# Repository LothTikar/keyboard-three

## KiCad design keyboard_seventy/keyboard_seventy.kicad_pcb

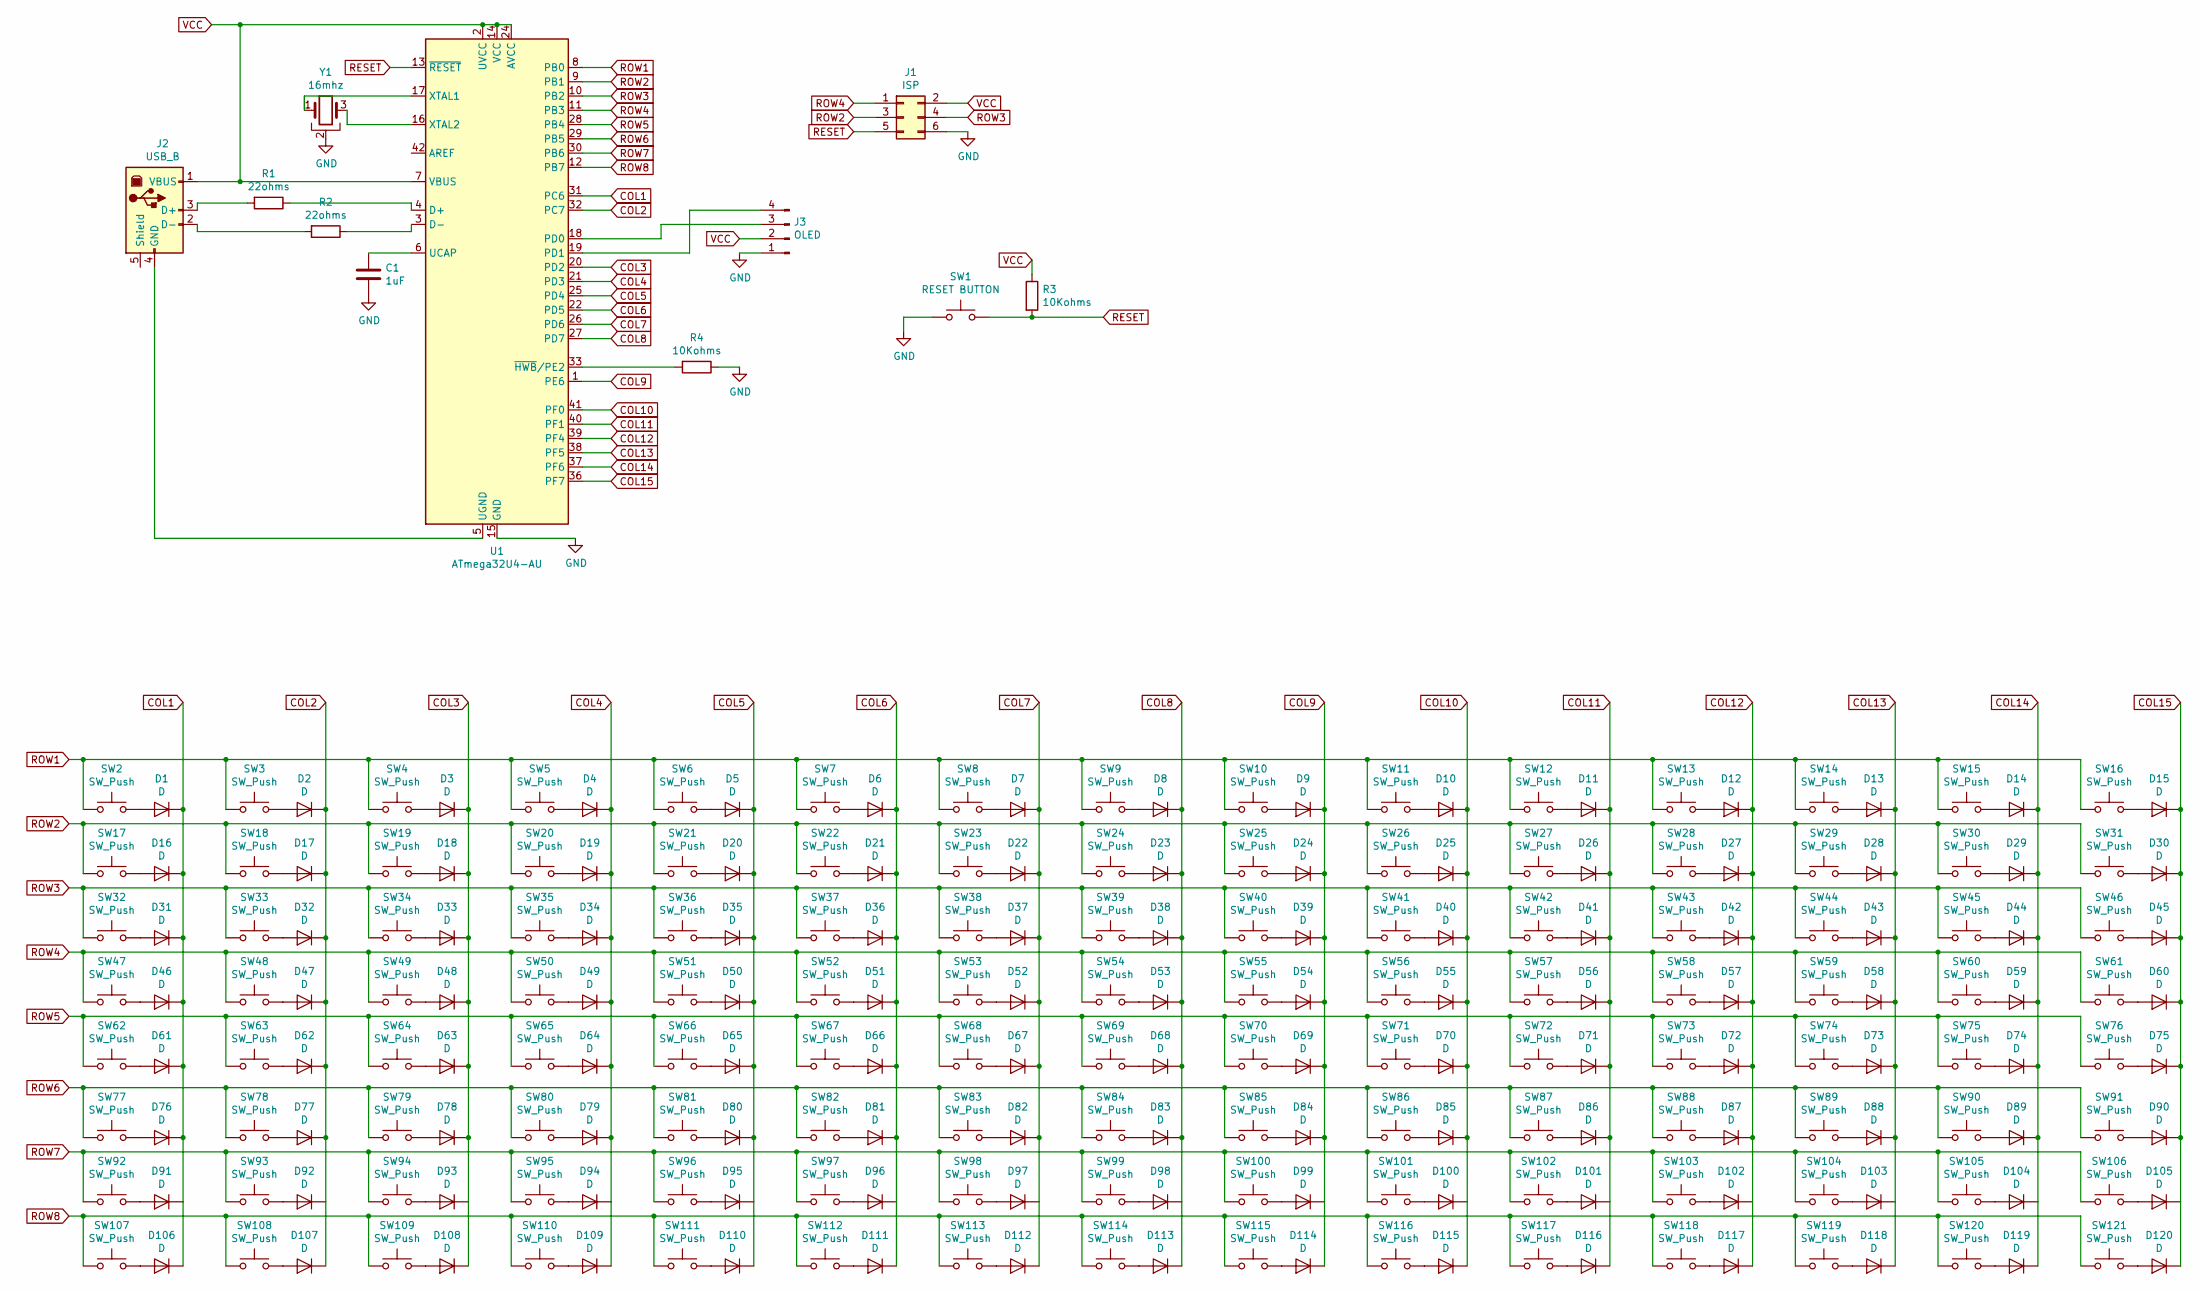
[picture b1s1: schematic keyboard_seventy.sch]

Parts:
C1: 1uF; C_Disc_D3.0mm_W1.6mm_P2.50mm
D1, D2, D3, D4, D5, D6, D7, D8, D9, D10, D11, D12, D13, D14, D15, D16, D17, D18, D19, D20, D21, D22, D23, D24, D25, D26, D27, D28, D29, D30, D31, D32, D33, D34, D35, D36, D37, D38, D39, D40, D41, D42, D43, D44, D45, D46, D47, D48, D49, D50, D51, D52, D53, D54, D55, D56, D57, D58, D59, D60, D61, D62, D63, D64, D65, D66, D67, D68, D69, D70, D71, D72, D73, D74, D75, D76, D77, D78, D79, D80, D81, D82, D83, D84, D85, D86, D87, D88, D89, D90, D91, D92, D93, D94, D95, D96, D97, D98, D99, D100, D101, D102, D103, D104, D105, D106, D107, D108, D109, D110, D111, D112, D113, D114, D115, D116, D117, D118, D119, D120: D; D_A-405_P7.62mm_Horizontal
J1: ISP; PinHeader_2x03_P2.54mm_Vertical
J2: USB_B; USB_B_OST_USB-B1HSxx_Horizontal
J3: OLED; PinHeader_1x04_P2.54mm_Vertical
R1, R2: 22ohms; R_Axial_DIN0207_L6.3mm_D2.5mm_P10.16mm_Horizontal
R3, R4: 10Kohms; R_Axial_DIN0207_L6.3mm_D2.5mm_P10.16mm_Horizontal
SW1: RESET BUTTON; SW_PUSH-12mm
SW2, SW3, SW4, SW5, SW6, SW7, SW8, SW9, SW10, SW11, SW12, SW13, SW14, SW15, SW16, SW17, SW18, SW19, SW20, SW21, SW22, SW23, SW24, SW25, SW26, SW27, SW28, SW29, SW30, SW31, SW32, SW33, SW34, SW35, SW36, SW37, SW38, SW39, SW40, SW41, SW42, SW43, SW44, SW45, SW46, SW47, SW48, SW49, SW50, SW51, SW52, SW53, SW54, SW55, SW56, SW57, SW58, SW59, SW60, SW61, SW62, SW63, SW64, SW65, SW66, SW67, SW68, SW69, SW70, SW71, SW72, SW73, SW74, SW75, SW76, SW77, SW78, SW79, SW80, SW81, SW82, SW83, SW84, SW85, SW86, SW87, SW88, SW89, SW90, SW91, SW92, SW93, SW94, SW95, SW96, SW97, SW98, SW99, SW100, SW101, SW102, SW103, SW104, SW105, SW106, SW107, SW108, SW109, SW110, SW111, SW112, SW113, SW114, SW115, SW116, SW117, SW118, SW119, SW120, SW121: SW_Push; PG1350_socket
U1: ATmega32U4-AU; TQFP-44_10x10mm_P0.8mm
Y1: 16mhz; Resonator-3Pin_W10.0mm_H5.0mm

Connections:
COL1: D1.1 (K), D16.1 (K), D31.1 (K), D46.1 (K), D61.1 (K), D76.1 (K), D91.1 (K), D106.1 (K), U1.31 (PC6)
COL2: D2.1 (K), D17.1 (K), D32.1 (K), D47.1 (K), D62.1 (K), D77.1 (K), D92.1 (K), D107.1 (K), U1.32 (PC7)
COL3: D3.1 (K), D18.1 (K), D33.1 (K), D48.1 (K), D63.1 (K), D78.1 (K), D93.1 (K), D108.1 (K), U1.20 (PD2)
COL4: D4.1 (K), D19.1 (K), D34.1 (K), D49.1 (K), D64.1 (K), D79.1 (K), D94.1 (K), D109.1 (K), U1.21 (PD3)
COL5: D5.1 (K), D20.1 (K), D35.1 (K), D50.1 (K), D65.1 (K), D80.1 (K), D95.1 (K), D110.1 (K), U1.25 (PD4)
COL6: D6.1 (K), D21.1 (K), D36.1 (K), D51.1 (K), D66.1 (K), D81.1 (K), D96.1 (K), D111.1 (K), U1.22 (PD5)
COL7: D7.1 (K), D22.1 (K), D37.1 (K), D52.1 (K), D67.1 (K), D82.1 (K), D97.1 (K), D112.1 (K), U1.26 (PD6)
COL8: D8.1 (K), D23.1 (K), D38.1 (K), D53.1 (K), D68.1 (K), D83.1 (K), D98.1 (K), D113.1 (K), U1.27 (PD7)
COL9: D9.1 (K), D24.1 (K), D39.1 (K), D54.1 (K), D69.1 (K), D84.1 (K), D99.1 (K), D114.1 (K), U1.1 (PE6)
COL10: D10.1 (K), D25.1 (K), D40.1 (K), D55.1 (K), D70.1 (K), D85.1 (K), D100.1 (K), D115.1 (K), U1.41 (PF0)
COL11: D11.1 (K), D26.1 (K), D41.1 (K), D56.1 (K), D71.1 (K), D86.1 (K), D101.1 (K), D116.1 (K), U1.40 (PF1)
COL12: D12.1 (K), D27.1 (K), D42.1 (K), D57.1 (K), D72.1 (K), D87.1 (K), D102.1 (K), D117.1 (K), U1.39 (PF4)
COL13: D13.1 (K), D28.1 (K), D43.1 (K), D58.1 (K), D73.1 (K), D88.1 (K), D103.1 (K), D118.1 (K), U1.38 (PF5)
COL14: D14.1 (K), D29.1 (K), D44.1 (K), D59.1 (K), D74.1 (K), D89.1 (K), D104.1 (K), D119.1 (K), U1.37 (PF6)
COL15: D15.1 (K), D30.1 (K), D45.1 (K), D60.1 (K), D75.1 (K), D90.1 (K), D105.1 (K), D120.1 (K), U1.36 (PF7)
GND: C1.2, J1.6, J3.1, R4.1, SW1.1, U1.15 (GND), U1.23 (GND), U1.35 (GND), U1.43 (GND), Y1.2
unnamed: C1.1, U1.6 (UCAP)
unnamed: D1.2 (A), SW2.2
unnamed: D2.2 (A), SW3.2
unnamed: D3.2 (A), SW4.2
unnamed: D4.2 (A), SW5.2
unnamed: D5.2 (A), SW6.2
unnamed: D6.2 (A), SW7.2
unnamed: D7.2 (A), SW8.2
unnamed: D8.2 (A), SW9.2
unnamed: D9.2 (A), SW10.2
unnamed: D10.2 (A), SW11.2
unnamed: D11.2 (A), SW12.2
unnamed: D12.2 (A), SW13.2
unnamed: D13.2 (A), SW14.2
unnamed: D14.2 (A), SW15.2
unnamed: D15.2 (A), SW16.2
unnamed: D16.2 (A), SW17.2
unnamed: D17.2 (A), SW18.2
unnamed: D18.2 (A), SW19.2
unnamed: D19.2 (A), SW20.2
unnamed: D20.2 (A), SW21.2
unnamed: D21.2 (A), SW22.2
unnamed: D22.2 (A), SW23.2
unnamed: D23.2 (A), SW24.2
unnamed: D24.2 (A), SW25.2
unnamed: D25.2 (A), SW26.2
unnamed: D26.2 (A), SW27.2
unnamed: D27.2 (A), SW28.2
unnamed: D28.2 (A), SW29.2
unnamed: D29.2 (A), SW30.2
unnamed: D30.2 (A), SW31.2
unnamed: D31.2 (A), SW32.2
unnamed: D32.2 (A), SW33.2
unnamed: D33.2 (A), SW34.2
unnamed: D34.2 (A), SW35.2
unnamed: D35.2 (A), SW36.2
unnamed: D36.2 (A), SW37.2
unnamed: D37.2 (A), SW38.2
unnamed: D38.2 (A), SW39.2
unnamed: D39.2 (A), SW40.2
unnamed: D40.2 (A), SW41.2
unnamed: D41.2 (A), SW42.2
unnamed: D42.2 (A), SW43.2
unnamed: D43.2 (A), SW44.2
unnamed: D44.2 (A), SW45.2
unnamed: D45.2 (A), SW46.2
unnamed: D46.2 (A), SW47.2
unnamed: D47.2 (A), SW48.2
unnamed: D48.2 (A), SW49.2
unnamed: D49.2 (A), SW50.2
unnamed: D50.2 (A), SW51.2
unnamed: D51.2 (A), SW52.2
unnamed: D52.2 (A), SW53.2
unnamed: D53.2 (A), SW54.2
unnamed: D54.2 (A), SW55.2
unnamed: D55.2 (A), SW56.2
unnamed: D56.2 (A), SW57.2
unnamed: D57.2 (A), SW58.2
unnamed: D58.2 (A), SW59.2
unnamed: D59.2 (A), SW60.2
unnamed: D60.2 (A), SW61.2
unnamed: D61.2 (A), SW62.2
unnamed: D62.2 (A), SW63.2
unnamed: D63.2 (A), SW64.2
unnamed: D64.2 (A), SW65.2
unnamed: D65.2 (A), SW66.2
unnamed: D66.2 (A), SW67.2
unnamed: D67.2 (A), SW68.2
unnamed: D68.2 (A), SW69.2
unnamed: D69.2 (A), SW70.2
unnamed: D70.2 (A), SW71.2
unnamed: D71.2 (A), SW72.2
unnamed: D72.2 (A), SW73.2
unnamed: D73.2 (A), SW74.2
unnamed: D74.2 (A), SW75.2
unnamed: D75.2 (A), SW76.2
unnamed: D76.2 (A), SW77.2
unnamed: D77.2 (A), SW78.2
unnamed: D78.2 (A), SW79.2
unnamed: D79.2 (A), SW80.2
unnamed: D80.2 (A), SW81.2
unnamed: D81.2 (A), SW82.2
unnamed: D82.2 (A), SW83.2
unnamed: D83.2 (A), SW84.2
unnamed: D84.2 (A), SW85.2
unnamed: D85.2 (A), SW86.2
unnamed: D86.2 (A), SW87.2
unnamed: D87.2 (A), SW88.2
unnamed: D88.2 (A), SW89.2
unnamed: D89.2 (A), SW90.2
unnamed: D90.2 (A), SW91.2
unnamed: D91.2 (A), SW92.2
unnamed: D92.2 (A), SW93.2
unnamed: D93.2 (A), SW94.2
unnamed: D94.2 (A), SW95.2
unnamed: D95.2 (A), SW96.2
unnamed: D96.2 (A), SW97.2
unnamed: D97.2 (A), SW98.2
unnamed: D98.2 (A), SW99.2
unnamed: D99.2 (A), SW100.2
unnamed: D100.2 (A), SW101.2
unnamed: D101.2 (A), SW102.2
unnamed: D102.2 (A), SW103.2
unnamed: D103.2 (A), SW104.2
unnamed: D104.2 (A), SW105.2
unnamed: D105.2 (A), SW106.2
unnamed: D106.2 (A), SW107.2
unnamed: D107.2 (A), SW108.2
unnamed: D108.2 (A), SW109.2
unnamed: D109.2 (A), SW110.2
unnamed: D110.2 (A), SW111.2
unnamed: D111.2 (A), SW112.2
unnamed: D112.2 (A), SW113.2
unnamed: D113.2 (A), SW114.2
unnamed: D114.2 (A), SW115.2
unnamed: D115.2 (A), SW116.2
unnamed: D116.2 (A), SW117.2
unnamed: D117.2 (A), SW118.2
unnamed: D118.2 (A), SW119.2
unnamed: D119.2 (A), SW120.2
unnamed: D120.2 (A), SW121.2
unnamed: J2.2 (D-), R2.2
unnamed: J2.3 (D+), R1.2
unnamed: J2.4 (GND), U1.5 (UGND)
unnamed: J3.3, U1.18 (PD0)
unnamed: J3.4, U1.19 (PD1)
unnamed: R1.1, U1.4 (D+)
unnamed: R2.1, U1.3 (D-)
unnamed: R4.2, U1.33 (~HWB~/PE2)
unnamed: U1.16 (XTAL2), Y1.3
unnamed: U1.17 (XTAL1), Y1.1
RESET: J1.5, R3.2, SW1.2, U1.13 (~RESET)
ROW1: SW2.1, SW3.1, SW4.1, SW5.1, SW6.1, SW7.1, SW8.1, SW9.1, SW10.1, SW11.1, SW12.1, SW13.1, SW14.1, SW15.1, SW16.1, U1.8 (PB0)
ROW2: J1.3, SW17.1, SW18.1, SW19.1, SW20.1, SW21.1, SW22.1, SW23.1, SW24.1, SW25.1, SW26.1, SW27.1, SW28.1, SW29.1, SW30.1, SW31.1, U1.9 (PB1)
ROW3: J1.4, SW32.1, SW33.1, SW34.1, SW35.1, SW36.1, SW37.1, SW38.1, SW39.1, SW40.1, SW41.1, SW42.1, SW43.1, SW44.1, SW45.1, SW46.1, U1.10 (PB2)
ROW4: J1.1, SW47.1, SW48.1, SW49.1, SW50.1, SW51.1, SW52.1, SW53.1, SW54.1, SW55.1, SW56.1, SW57.1, SW58.1, SW59.1, SW60.1, SW61.1, U1.11 (PB3)
ROW5: SW62.1, SW63.1, SW64.1, SW65.1, SW66.1, SW67.1, SW68.1, SW69.1, SW70.1, SW71.1, SW72.1, SW73.1, SW74.1, SW75.1, SW76.1, U1.28 (PB4)
ROW6: SW77.1, SW78.1, SW79.1, SW80.1, SW81.1, SW82.1, SW83.1, SW84.1, SW85.1, SW86.1, SW87.1, SW88.1, SW89.1, SW90.1, SW91.1, U1.29 (PB5)
ROW7: SW92.1, SW93.1, SW94.1, SW95.1, SW96.1, SW97.1, SW98.1, SW99.1, SW100.1, SW101.1, SW102.1, SW103.1, SW104.1, SW105.1, SW106.1, U1.30 (PB6)
ROW8: SW107.1, SW108.1, SW109.1, SW110.1, SW111.1, SW112.1, SW113.1, SW114.1, SW115.1, SW116.1, SW117.1, SW118.1, SW119.1, SW120.1, SW121.1, U1.12 (PB7)
VCC: J1.2, J2.1 (VBUS), J3.2, R3.1, U1.2 (UVCC), U1.7 (VBUS), U1.14 (VCC), U1.24 (AVCC), U1.34 (VCC), U1.44 (AVCC)

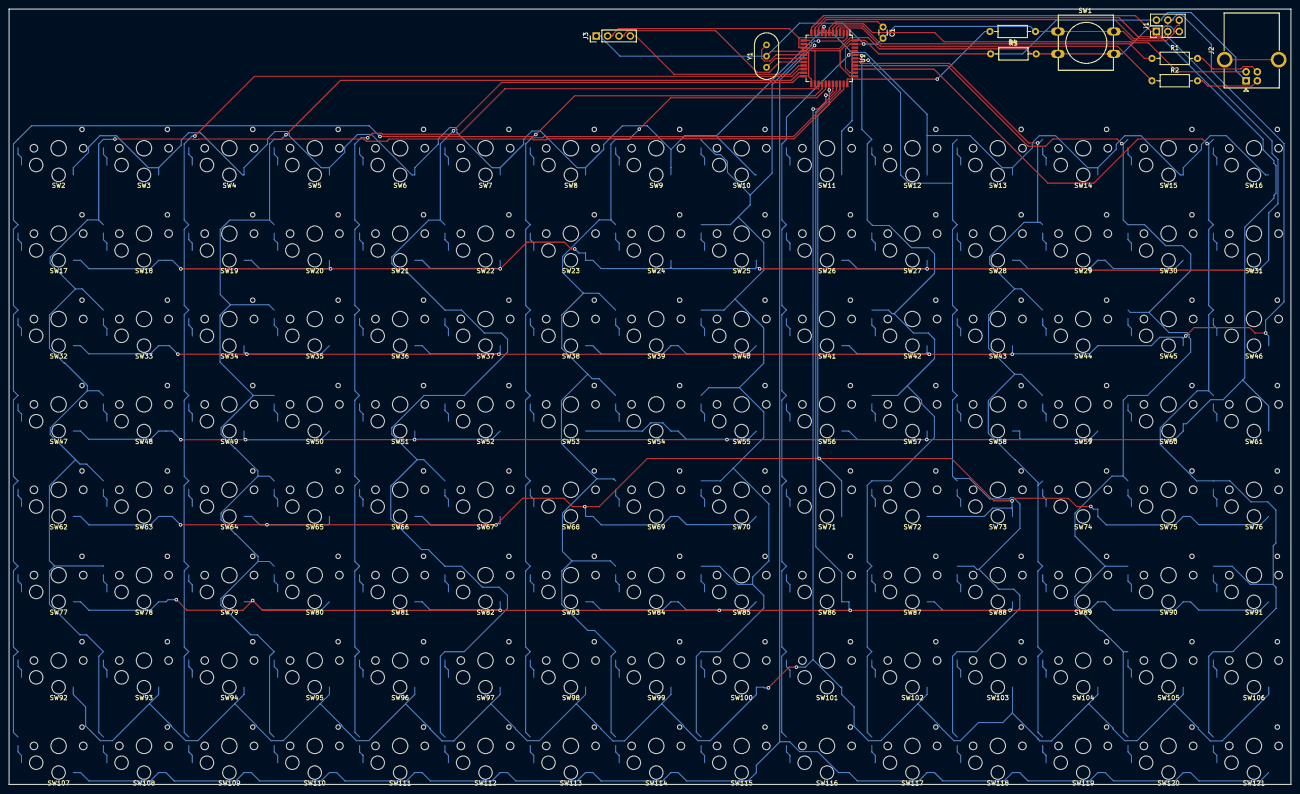
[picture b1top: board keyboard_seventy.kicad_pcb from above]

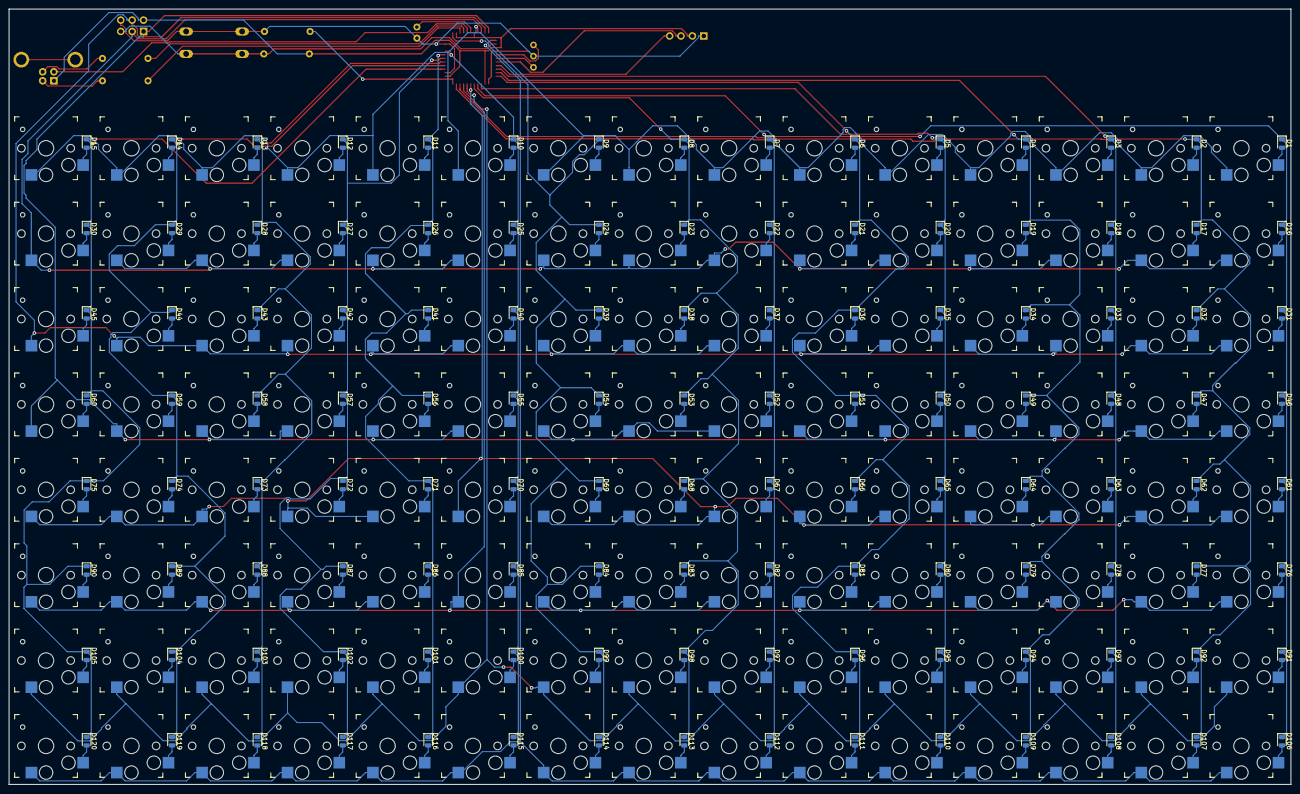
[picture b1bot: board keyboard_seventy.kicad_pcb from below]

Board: 2 copper layers, 286.0 x 173.0 mm, 251 parts (120 on the bottom side), 157 nets.

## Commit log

2019-11-27 added current progress
2019-11-27 labled and arranged keys
2019-11-27 arranged and numbered diodes
2019-11-27 board outline and component placement
2019-11-28 smd diodes and some routing
2019-11-30 wired though should check connecting gnds
